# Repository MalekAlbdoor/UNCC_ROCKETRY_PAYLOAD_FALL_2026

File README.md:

# UNCC Rocketry Payload, Fall 2026

Custom avionics board for the UNC Charlotte rocketry club's transonic payload. It logs flight data, tracks position, sends live telemetry and pad status to a ground station, and controls an onboard camera.

## Layout

The schematic is split into hierarchical sheets, all tied together on the root sheet:

| Sheet | Contents |
|---|---|
| POWER | 5V buck, 3.3V regulator, power LED, bring-up jumpers and camera power switch |
| MCU | Microcontroller, clock, reset/boot, battery voltage sense, buzzer and status LED |
| SENSORS | Inertial, pressure and environmental sensors |
| RF | LoRa telemetry radio and GPS |
| FLASH | Onboard flight data storage |
| CONNECTORS | Battery input protection, arming switch, debug header, camera and USB-C |

## Tools

Designed in KiCad 10. Open `UNCC_ROCKETRY_PAYLOAD_FALL_2026.kicad_pro` to get started.

No KiCad? Download [Schematic.pdf](Schematic.pdf) to view the full schematic.

## Dashboard
Take a look at live telemetry at telemetry.malekalbdoor.com

## Status

Schematic in progress. Firmware is being developed on breadboarded breakout boards in parallel. PCB layout has not started.

## License

Copyright (c) 2026 Malek Albdoor.

Everything in this repository (schematics, PCB layout, 3D models, firmware and the telemetry dashboard) is licensed under [Creative Commons Attribution-NonCommercial 4.0](LICENSE) (CC BY-NC 4.0).

- **You can** use, copy, modify and share it for noncommercial purposes, such as personal projects, school teams and research.
- **You must** credit both Malek Albdoor and the [Charlotte Rocketry Club](https://www.charlotterocketry.org/) at UNC Charlotte, link back to this repository, and say if you changed anything.
- **You cannot** use it, or anything made from it, to make money without written permission.

Credit it like this:

> Based on the UNCC Rocketry payload board by Malek Albdoor and the Charlotte Rocketry Club at UNC Charlotte (https://www.charlotterocketry.org/), https://github.com/MalekAlbdoor/UNCC_ROCKETRY_PAYLOAD_FALL_2026, CC BY-NC 4.0.

Libraries and KiCad library parts used by this project keep their own licenses.

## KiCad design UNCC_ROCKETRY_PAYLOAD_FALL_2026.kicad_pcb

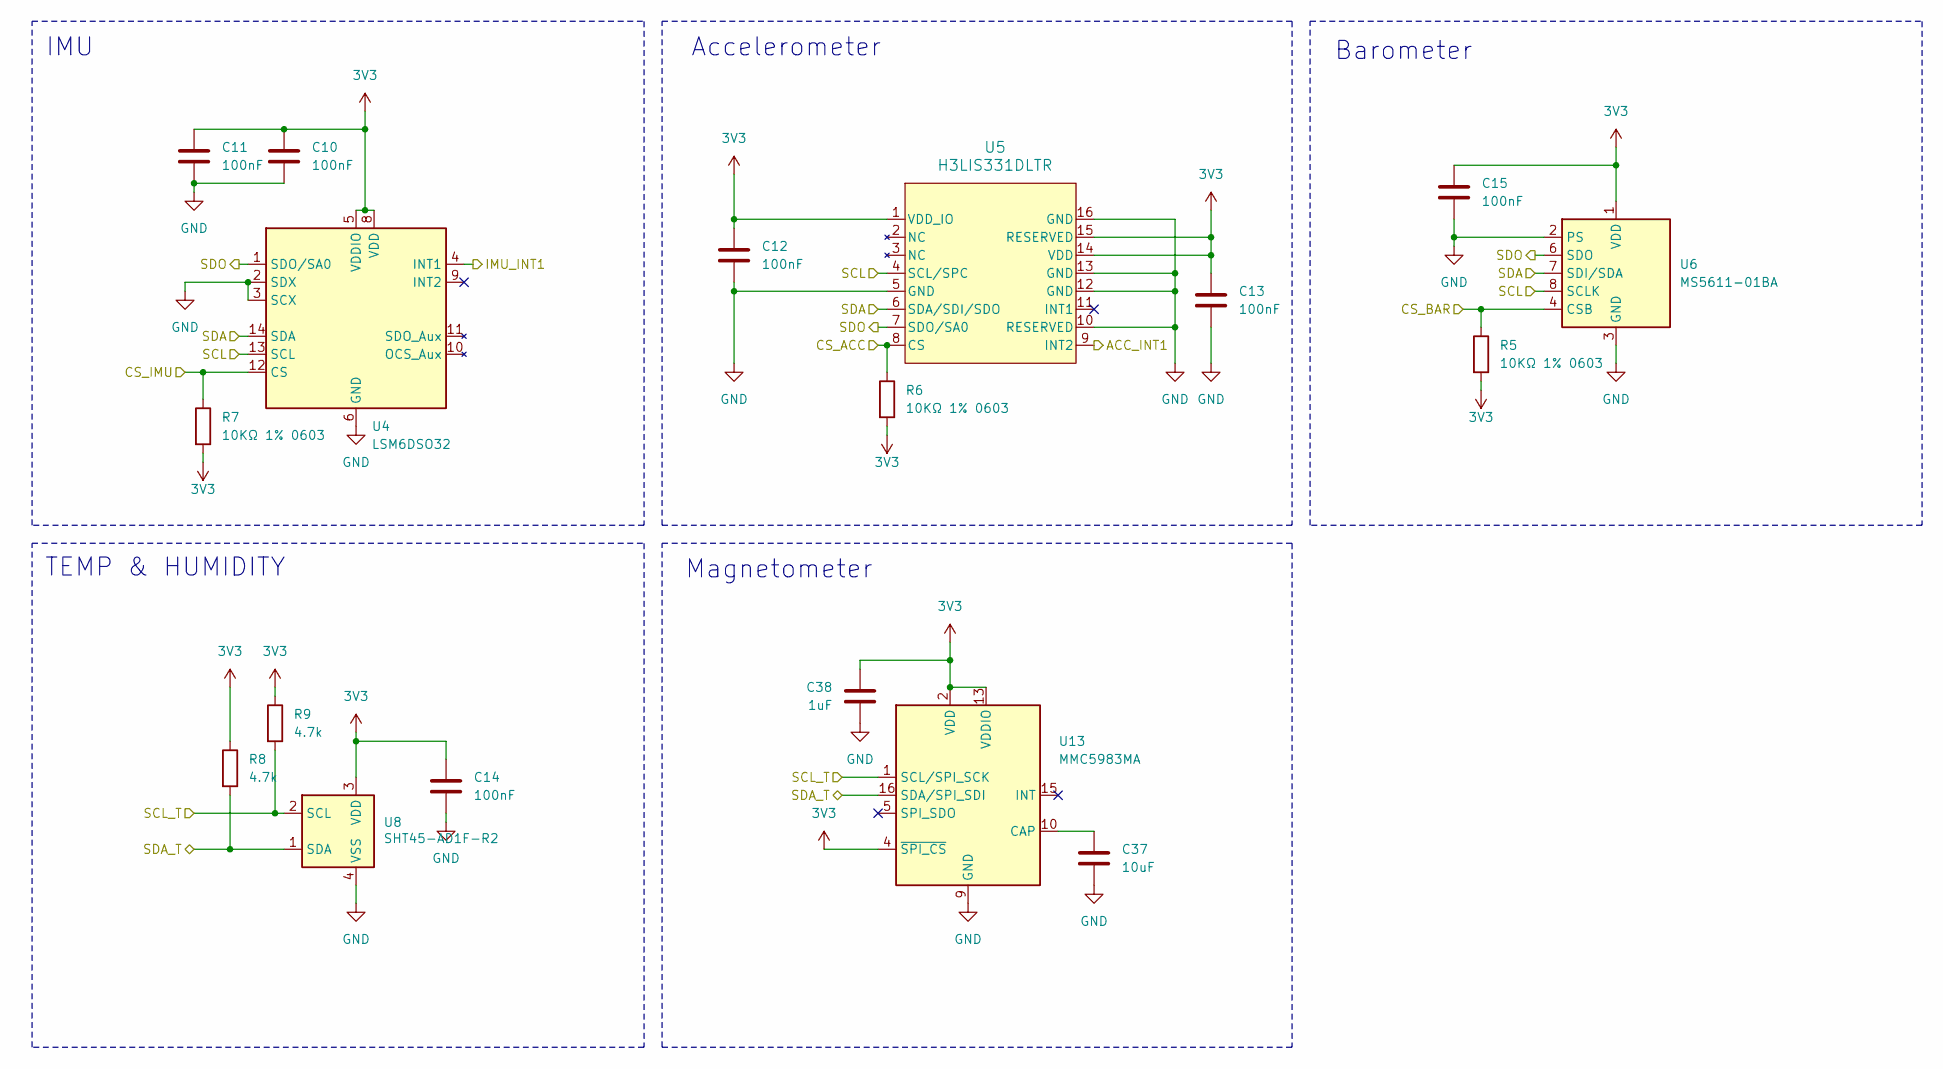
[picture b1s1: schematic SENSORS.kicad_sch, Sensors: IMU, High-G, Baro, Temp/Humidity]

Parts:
C10, C11, C12, C13, C14, C15: 100nF; C_0603_1608Metric_Pad1.08x0.95mm_HandSolder
C37: 10uF; C_0805_2012Metric_Pad1.18x1.45mm_HandSolder
C38: 1uF; C_0603_1608Metric_Pad1.08x0.95mm_HandSolder
R5, R6, R7: 10KΩ 1% 0603; R_0603_1608Metric_Pad0.98x0.95mm_HandSolder
R8, R9: 4.7k; R_0603_1608Metric_Pad0.98x0.95mm_HandSolder
U4: LSM6DSO32; LGA-14_3x2.5mm_P0.5mm_LayoutBorder3x4y
U5: H3LIS331DLTR; LGA-16_3x3mm_P0.5mm_LayoutBorder3x5y
U6: MS5611-01BA; LGA-8_3x5mm_P1.25mm
U8: SHT45-AD1F-R2; Sensirion_DFN-4_1.5x1.5mm_P0.8mm_SHT4x_NoCentralPad
U13: MMC5983MA; LGA-16_3x3mm_P0.5mm

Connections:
3V3: C10.1, C11.1, C12.1, C13.1, C14.1, C15.1, C38.1, R5.2, R6.2, R7.2, R8.1, R9.1, U4.5 (VDDIO), U4.8 (VDD), U5.1 (VDD_IO), U5.14 (VDD), U5.15 (RESERVED), U6.1 (VDD), U8.3 (VDD), U13.2 (VDD), U13.4 (~SPI_CS), U13.13 (VDDIO); also elsewhere on the board
/MCU/ACC_INT1: U5.9 (INT2); also elsewhere on the board
/MCU/CS_ACC: R6.1, U5.8 (CS); also elsewhere on the board
/MCU/CS_BAR: R5.1, U6.4 (CSB), U6.5 (CSB); also elsewhere on the board
/MCU/CS_IMU: R7.1, U4.12 (CS); also elsewhere on the board
/MCU/IMU_INT1: U4.4 (INT1); also elsewhere on the board
/MCU/SCL: U4.13 (SCL), U5.4 (SCL/SPC), U6.8 (SCLK); also elsewhere on the board
/MCU/SDA: U4.14 (SDA), U5.6 (SDA/SDI/SDO), U6.7 (SDI/SDA); also elsewhere on the board
/MCU/SDO: U4.1 (SDO/SA0), U5.7 (SDO/SA0), U6.6 (SDO); also elsewhere on the board
/SCL_T: R9.2, U8.2 (SCL), U13.1 (SCL/SPI_SCK); also elsewhere on the board
/SDA_T: R8.2, U8.1 (SDA), U13.16 (SDA/SPI_SDI); also elsewhere on the board
GND: C10.2, C11.2, C12.2, C13.2, C14.2, C15.2, C37.2, C38.2, U4.2 (SDX), U4.3 (SCX), U4.6 (GND), U4.7 (GND), U5.5 (GND), U5.10 (RESERVED), U5.12 (GND), U5.13 (GND), U5.16 (GND), U6.2 (PS), U6.3 (GND), U8.4 (VSS), U13.9 (GND), U13.11 (GND); also elsewhere on the board
unnamed: C37.1, U13.10 (CAP)

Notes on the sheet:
Magnetometer
TEMP & HUMIDITY
Barometer
Accelerometer
IMU

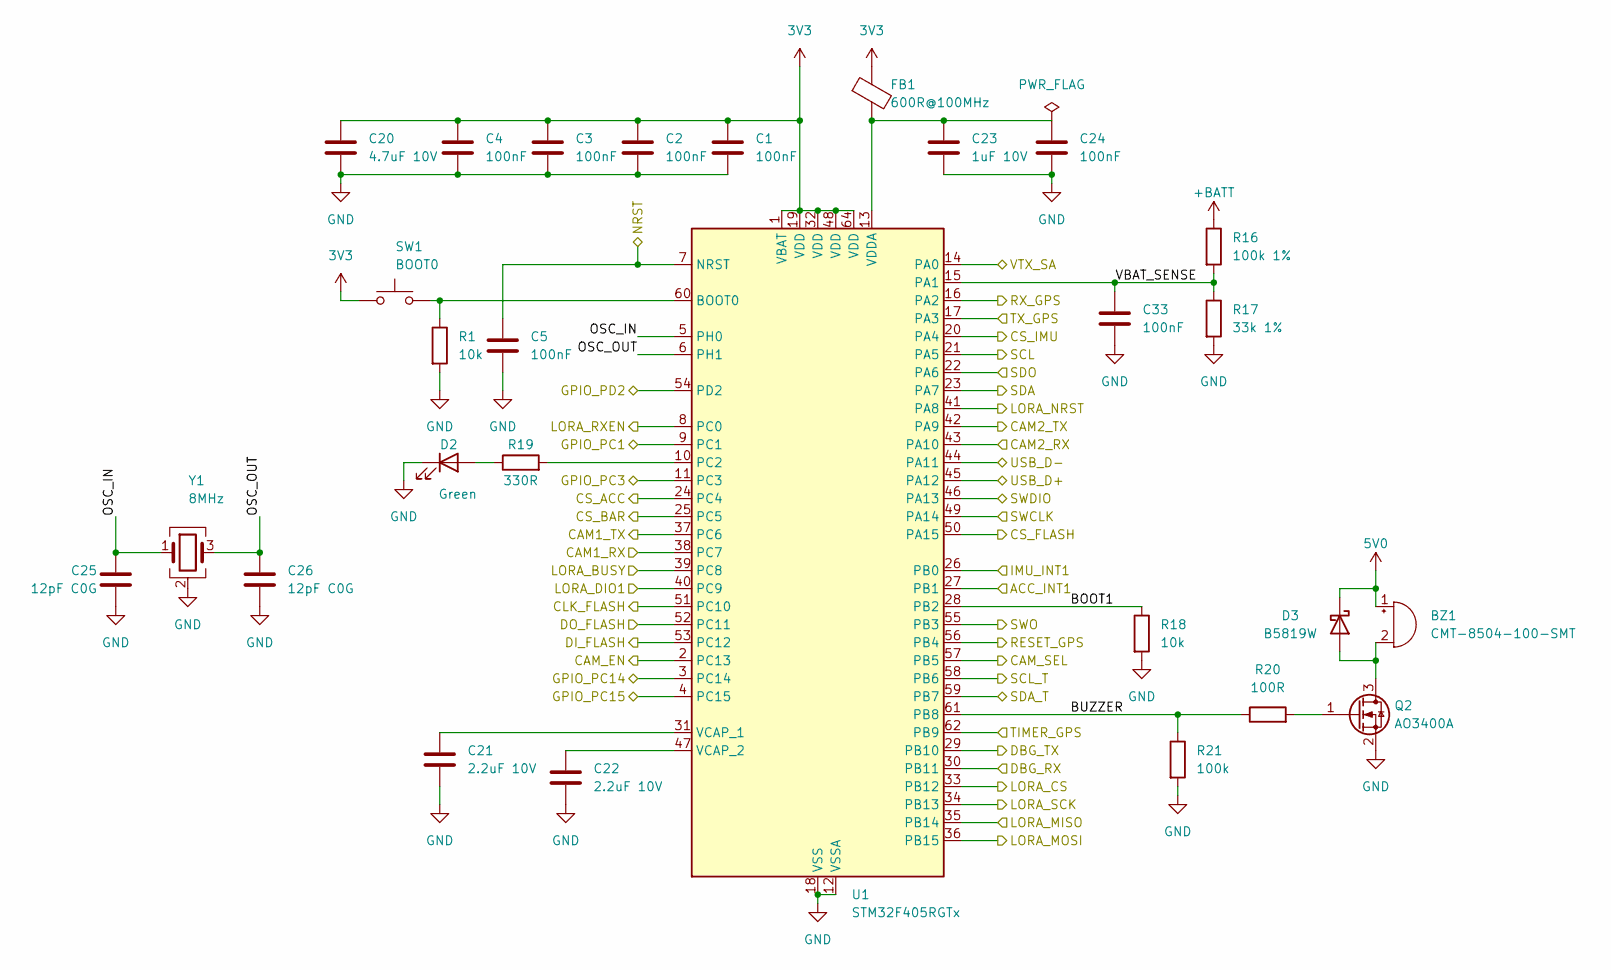
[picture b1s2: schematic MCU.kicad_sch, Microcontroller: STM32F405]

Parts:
BZ1: CMT-8504-100-SMT; MagneticBuzzer_CUI_CMT-8504-100-SMT
C1, C2, C3, C4, C5, C24, C33: 100nF; C_0603_1608Metric_Pad1.08x0.95mm_HandSolder
C20: 4.7uF 10V; C_0603_1608Metric_Pad1.08x0.95mm_HandSolder
C21, C22: 2.2uF 10V; C_0603_1608Metric_Pad1.08x0.95mm_HandSolder
C23: 1uF 10V; C_0603_1608Metric_Pad1.08x0.95mm_HandSolder
C25, C26: 12pF C0G; C_0603_1608Metric_Pad1.08x0.95mm_HandSolder
D2: Green; LED_0603_1608Metric_Pad1.05x0.95mm_HandSolder
D3: B5819W; D_SOD-123
FB1: 600R@100MHz; L_0603_1608Metric_Pad1.05x0.95mm_HandSolder
Q2: AO3400A; SOT-23
R1, R18: 10k; R_0603_1608Metric_Pad0.98x0.95mm_HandSolder
R16: 100k 1%; R_0603_1608Metric_Pad0.98x0.95mm_HandSolder
R17: 33k 1%; R_0603_1608Metric_Pad0.98x0.95mm_HandSolder
R19: 330R; R_0603_1608Metric_Pad0.98x0.95mm_HandSolder
R20: 100R; R_0603_1608Metric_Pad0.98x0.95mm_HandSolder
R21: 100k; R_0603_1608Metric_Pad0.98x0.95mm_HandSolder
SW1: BOOT0; SW_SPST_TL3342
U1: STM32F405RGTx; LQFP-64_10x10mm_P0.5mm
Y1: 8MHz; Crystal_SMD_Abracon_ABM3B-4Pin_5.0x3.2mm; MPN ABM3B-8.000MHZ-10-D-1-G-T

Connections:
3V3: C1.1, C2.1, C3.1, C4.1, C20.1, FB1.1, SW1.1, U1.1 (VBAT), U1.19 (VDD), U1.32 (VDD), U1.48 (VDD), U1.64 (VDD); also elsewhere on the board
5V0: BZ1.1 (+), D3.1 (K); also elsewhere on the board
+BATT: R16.1; also elsewhere on the board
/CONNECTORS/CAM1_RX: U1.38 (PC7); also elsewhere on the board
/CONNECTORS/CAM1_TX: U1.37 (PC6); also elsewhere on the board
/CONNECTORS/CAM2_RX: U1.43 (PA10); also elsewhere on the board
/CONNECTORS/CAM2_TX: U1.42 (PA9); also elsewhere on the board
/CONNECTORS/CAM_SEL: U1.57 (PB5); also elsewhere on the board
/CONNECTORS/DBG_RX: U1.30 (PB11); also elsewhere on the board
/CONNECTORS/DBG_TX: U1.29 (PB10); also elsewhere on the board
/CONNECTORS/GPIO_PC1: U1.9 (PC1); also elsewhere on the board
/CONNECTORS/GPIO_PC3: U1.11 (PC3); also elsewhere on the board
/CONNECTORS/GPIO_PC14: U1.3 (PC14); also elsewhere on the board
/CONNECTORS/GPIO_PC15: U1.4 (PC15); also elsewhere on the board
/CONNECTORS/NRST: C5.1, U1.7 (NRST); also elsewhere on the board
/CONNECTORS/SWCLK: U1.49 (PA14); also elsewhere on the board
/CONNECTORS/SWDIO: U1.46 (PA13); also elsewhere on the board
/CONNECTORS/SWO: U1.55 (PB3); also elsewhere on the board
/CONNECTORS/USB_D+: U1.45 (PA12); also elsewhere on the board
/CONNECTORS/USB_D-: U1.44 (PA11); also elsewhere on the board
/CONNECTORS/VTX_SA: U1.14 (PA0); also elsewhere on the board
/FLASH/CLK_FLASH: U1.51 (PC10); also elsewhere on the board
/FLASH/CS_FLASH: U1.50 (PA15); also elsewhere on the board
/FLASH/DI_FLASH: U1.53 (PC12); also elsewhere on the board
/FLASH/DO_FLASH: U1.52 (PC11); also elsewhere on the board
/MCU/ACC_INT1: U1.27 (PB1); also elsewhere on the board
/MCU/BOOT1: R18.1, U1.28 (PB2)
/MCU/BUZZER: R20.1, R21.1, U1.61 (PB8)
/MCU/CAM_EN: U1.2 (PC13); also elsewhere on the board
/MCU/CS_ACC: U1.24 (PC4); also elsewhere on the board
/MCU/CS_BAR: U1.25 (PC5); also elsewhere on the board
/MCU/CS_IMU: U1.20 (PA4); also elsewhere on the board
/MCU/GPIO_PD2: U1.54 (PD2)
/MCU/IMU_INT1: U1.26 (PB0); also elsewhere on the board
/MCU/LORA_BUSY: U1.39 (PC8); also elsewhere on the board
/MCU/LORA_CS: U1.33 (PB12); also elsewhere on the board
/MCU/LORA_DIO1: U1.40 (PC9); also elsewhere on the board
/MCU/LORA_MISO: U1.35 (PB14); also elsewhere on the board
/MCU/LORA_MOSI: U1.36 (PB15); also elsewhere on the board
/MCU/LORA_NRST: U1.41 (PA8); also elsewhere on the board
/MCU/LORA_RXEN: U1.8 (PC0); also elsewhere on the board
/MCU/LORA_SCK: U1.34 (PB13); also elsewhere on the board
/MCU/OSC_IN: C25.1, U1.5 (PH0), Y1.1
/MCU/OSC_OUT: C26.1, U1.6 (PH1), Y1.3
/MCU/RESET_GPS: U1.56 (PB4); also elsewhere on the board
/MCU/RX_GPS: U1.16 (PA2); also elsewhere on the board
/MCU/SCL: U1.21 (PA5); also elsewhere on the board
/MCU/SDA: U1.23 (PA7); also elsewhere on the board
/MCU/SDO: U1.22 (PA6); also elsewhere on the board
/MCU/TIMER_GPS: U1.62 (PB9); also elsewhere on the board
/MCU/TX_GPS: U1.17 (PA3); also elsewhere on the board
/MCU/VBAT_SENSE: C33.1, R16.2, R17.1, U1.15 (PA1)
/SCL_T: U1.58 (PB6); also elsewhere on the board
/SDA_T: U1.59 (PB7); also elsewhere on the board
GND: C1.2, C2.2, C3.2, C4.2, C5.2, C20.2, C21.2, C22.2, C23.2, C24.2, C25.2, C26.2, C33.2, D2.1 (K), Q2.2 (S), R1.2, R17.2, R18.2, R21.2, U1.12 (VSSA), U1.18 (VSS), U1.63 (VSS), Y1.2 (G), Y1.4 (G); also elsewhere on the board
unnamed: BZ1.2 (-), D3.2 (A), Q2.3 (D)
unnamed: D2.2 (A), R19.1
unnamed: Q2.1 (G), R20.2
unnamed: R1.1, SW1.2, U1.60 (BOOT0)
unnamed: R19.2, U1.10 (PC2)
unnamed: C21.1, U1.31 (VCAP_1)
unnamed: C22.1, U1.47 (VCAP_2)
unnamed: C23.1, C24.1, FB1.2, U1.13 (VDDA)

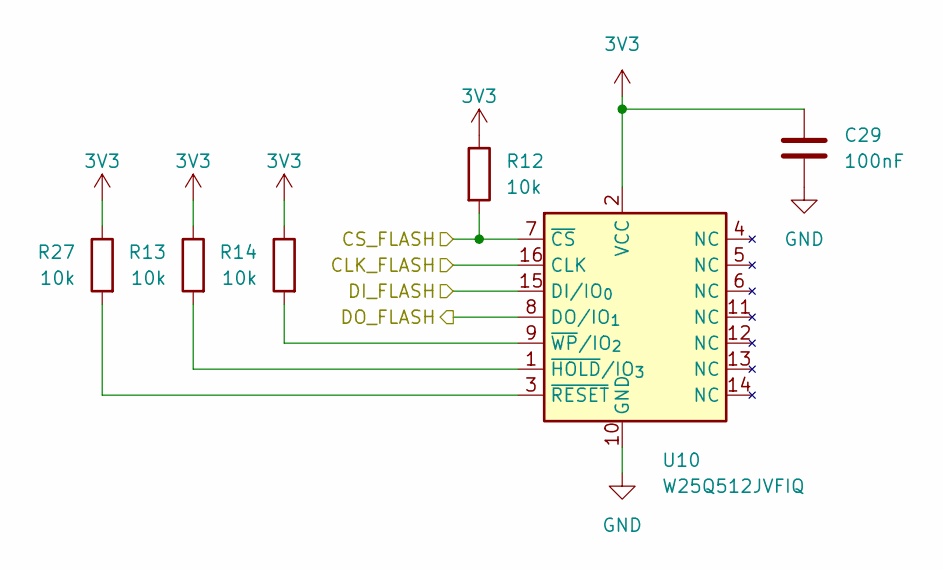
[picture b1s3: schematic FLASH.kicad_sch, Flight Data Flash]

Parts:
C29: 100nF; C_0603_1608Metric_Pad1.08x0.95mm_HandSolder
R12, R13, R14, R27: 10k; R_0603_1608Metric_Pad0.98x0.95mm_HandSolder
U10: W25Q512JVFIQ; SOIC-16W_7.5x10.3mm_P1.27mm

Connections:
3V3: C29.1, R12.1, R13.1, R14.1, R27.1, U10.2 (VCC); also elsewhere on the board
/FLASH/CLK_FLASH: U10.16 (CLK); also elsewhere on the board
/FLASH/CS_FLASH: R12.2, U10.7 (~CS); also elsewhere on the board
/FLASH/DI_FLASH: U10.15 (DI/IO_{0}); also elsewhere on the board
/FLASH/DO_FLASH: U10.8 (DO/IO_{1}); also elsewhere on the board
GND: C29.2, U10.10 (GND); also elsewhere on the board
unnamed: R13.2, U10.1 (~HOLD/IO_{3})
unnamed: R27.2, U10.3 (~RESET)
unnamed: R14.2, U10.9 (~WP/IO_{2})

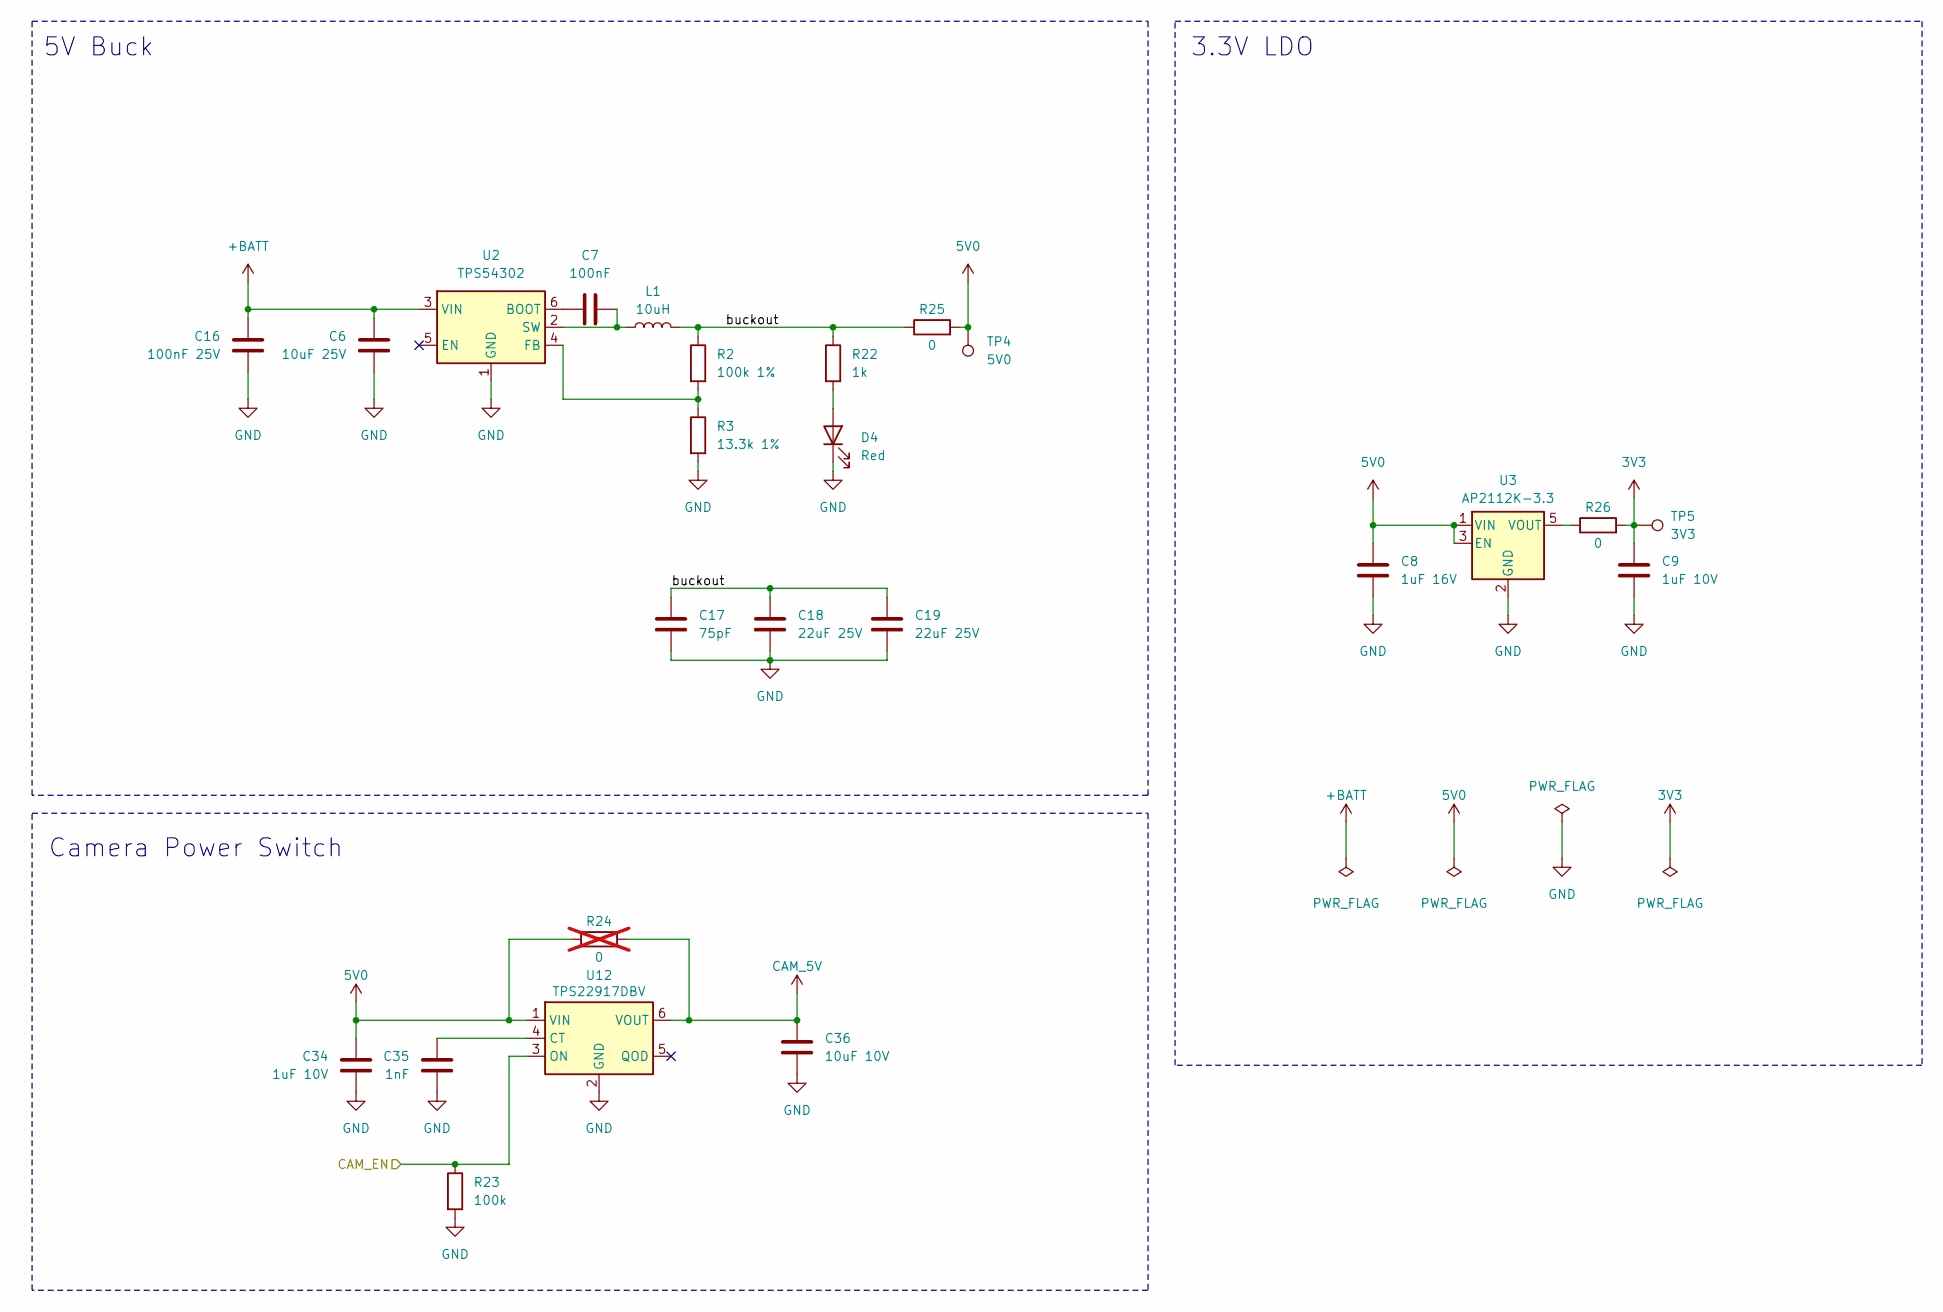
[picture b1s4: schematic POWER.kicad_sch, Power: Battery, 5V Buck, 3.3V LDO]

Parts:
C6: 10uF 25V; C_1206_3216Metric_Pad1.33x1.80mm_HandSolder
C7: 100nF; C_0603_1608Metric_Pad1.08x0.95mm_HandSolder
C8: 1uF 16V; C_0603_1608Metric_Pad1.08x0.95mm_HandSolder
C9, C34: 1uF 10V; C_0603_1608Metric_Pad1.08x0.95mm_HandSolder
C16: 100nF 25V; C_0603_1608Metric_Pad1.08x0.95mm_HandSolder
C17: 75pF; C_0603_1608Metric_Pad1.08x0.95mm_HandSolder
C18, C19: 22uF 25V; C_1206_3216Metric_Pad1.33x1.80mm_HandSolder
C35: 1nF; C_0603_1608Metric_Pad1.08x0.95mm_HandSolder
C36: 10uF 10V; C_0805_2012Metric_Pad1.18x1.45mm_HandSolder
D4: Red; LED_0603_1608Metric_Pad1.05x0.95mm_HandSolder
L1: 10uH; L_Wuerth_XHMI-6060; MPN 74439346100
R2: 100k 1%; R_0603_1608Metric_Pad0.98x0.95mm_HandSolder
R3: 13.3k 1%; R_0603_1608Metric_Pad0.98x0.95mm_HandSolder
R22: 1k; R_0603_1608Metric_Pad0.98x0.95mm_HandSolder
R23: 100k; R_0603_1608Metric_Pad0.98x0.95mm_HandSolder
R24: 0; R_0603_1608Metric_Pad0.98x0.95mm_HandSolder; not fitted
R25, R26: 0; R_0603_1608Metric_Pad0.98x0.95mm_HandSolder
TP4: 5V0; TestPoint_Pad_D1.5mm
TP5: 3V3; TestPoint_Pad_D1.5mm
U2: TPS54302; SOT-23-6
U3: AP2112K-3.3; SOT-23-5
U12: TPS22917DBV; SOT-23-6

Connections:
3V3: C9.1, R26.2, TP5.1 (1_1); also elsewhere on the board
5V0: C8.1, C34.1, R24.1, R25.2, TP4.1 (1_1), U3.1 (VIN), U3.3 (EN), U12.1 (VIN); also elsewhere on the board
+BATT: C6.1, C16.1, U2.3 (VIN); also elsewhere on the board
/MCU/CAM_EN: R23.1, U12.3 (ON); also elsewhere on the board
/POWER/buckout: C17.1, C18.1, C19.1, L1.2, R2.1, R22.1, R25.1
CAM_5V: C36.1, R24.2, U12.6 (VOUT); also elsewhere on the board
GND: C6.2, C8.2, C9.2, C16.2, C17.2, C18.2, C19.2, C34.2, C35.2, C36.2, D4.1 (K), R3.2, R23.2, U2.1 (GND), U3.2 (GND), U12.2 (GND); also elsewhere on the board
unnamed: D4.2 (A), R22.2
unnamed: C7.1, U2.6 (BOOT)
unnamed: R2.2, R3.1, U2.4 (FB)
unnamed: C7.2, L1.1, U2.2 (SW)
unnamed: R26.1, U3.5 (VOUT)
unnamed: C35.1, U12.4 (CT)

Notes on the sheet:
3.3V LDO
5V Buck
Camera Power Switch

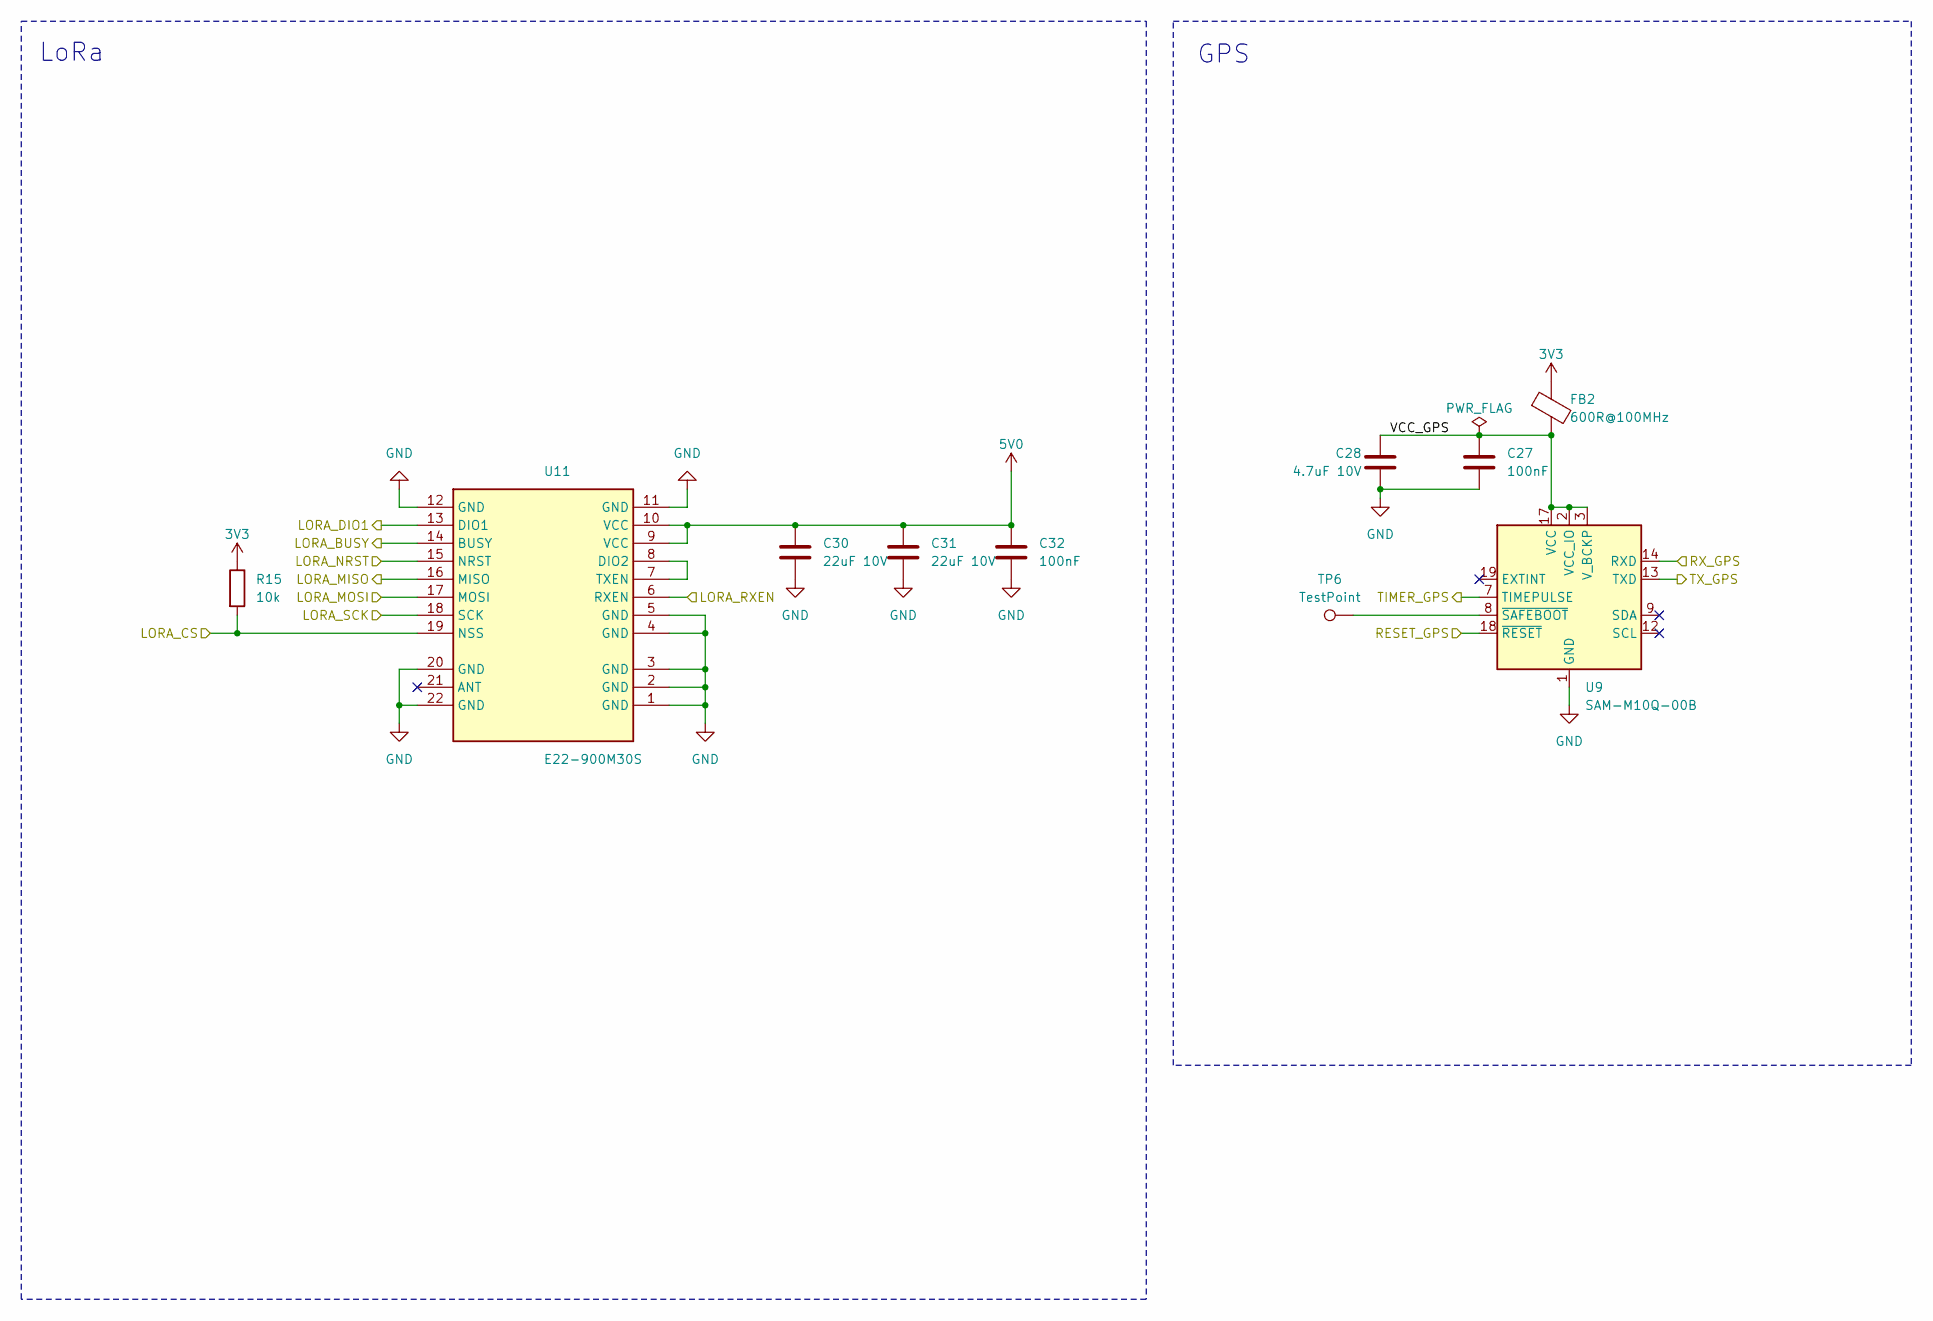
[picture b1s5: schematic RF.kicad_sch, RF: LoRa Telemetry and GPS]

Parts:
C27, C32: 100nF; C_0603_1608Metric_Pad1.08x0.95mm_HandSolder
C28: 4.7uF 10V; C_0603_1608Metric_Pad1.08x0.95mm_HandSolder
C30, C31: 22uF 10V; C_1206_3216Metric_Pad1.33x1.80mm_HandSolder
FB2: 600R@100MHz; L_0603_1608Metric_Pad1.05x0.95mm_HandSolder
R15: 10k; R_0603_1608Metric_Pad0.98x0.95mm_HandSolder
TP6: TestPoint; TestPoint_Pad_D1.5mm
U9: SAM-M10Q-00B; ublox_SAM-M8Q
U11: E22-900M30S; WIRELM-SMD_E22-900M30S

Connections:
3V3: FB2.1, R15.1; also elsewhere on the board
5V0: C30.1, C31.1, C32.1, U11.9 (VCC), U11.10 (VCC); also elsewhere on the board
/MCU/LORA_BUSY: U11.14 (BUSY); also elsewhere on the board
/MCU/LORA_CS: R15.2, U11.19 (NSS); also elsewhere on the board
/MCU/LORA_DIO1: U11.13 (DIO1); also elsewhere on the board
/MCU/LORA_MISO: U11.16 (MISO); also elsewhere on the board
/MCU/LORA_MOSI: U11.17 (MOSI); also elsewhere on the board
/MCU/LORA_NRST: U11.15 (NRST); also elsewhere on the board
/MCU/LORA_RXEN: U11.6 (RXEN); also elsewhere on the board
/MCU/LORA_SCK: U11.18 (SCK); also elsewhere on the board
/MCU/RESET_GPS: U9.18 (~RESET); also elsewhere on the board
/MCU/RX_GPS: U9.14 (RXD); also elsewhere on the board
/MCU/TIMER_GPS: U9.7 (TIMEPULSE); also elsewhere on the board
/MCU/TX_GPS: U9.13 (TXD); also elsewhere on the board
/RF/VCC_GPS: C27.1, C28.1, FB2.2, U9.2 (VCC_IO), U9.3 (V_BCKP), U9.17 (VCC)
GND: C27.2, C28.2, C30.2, C31.2, C32.2, U9.1 (GND), U9.4 (GND), U9.5 (GND), U9.6 (GND), U9.10 (GND), U9.11 (GND), U9.15 (GND), U9.16 (GND), U9.20 (GND), U11.1 (GND), U11.2 (GND), U11.3 (GND), U11.4 (GND), U11.5 (GND), U11.11 (GND), U11.12 (GND), U11.20 (GND), U11.22 (GND); also elsewhere on the board
unnamed: TP6.1 (1_1), U9.8 (~SAFEBOOT)
unnamed: U11.7 (TXEN), U11.8 (DIO2)

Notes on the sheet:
LoRa
GPS

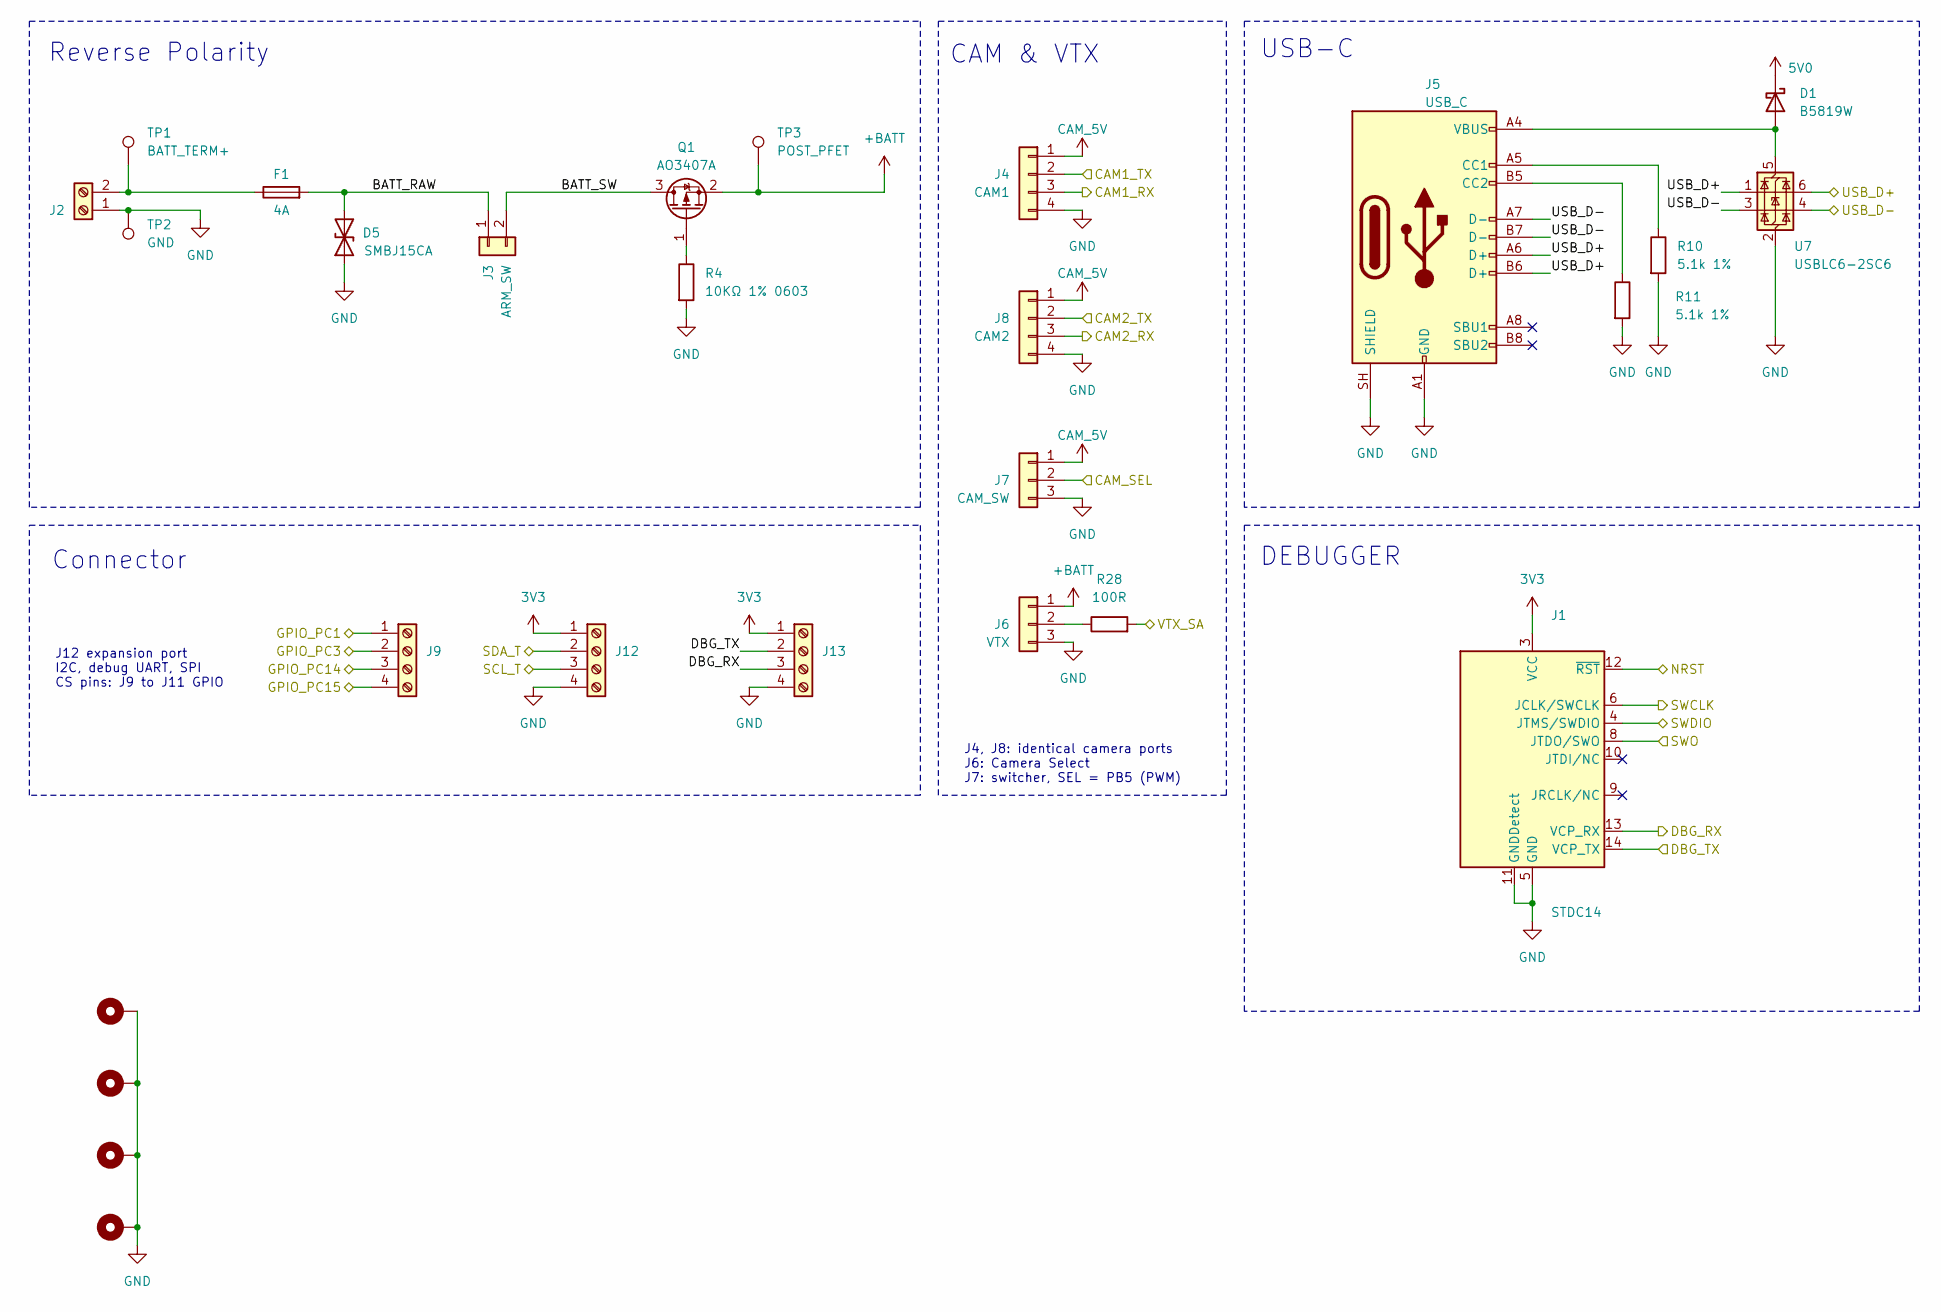
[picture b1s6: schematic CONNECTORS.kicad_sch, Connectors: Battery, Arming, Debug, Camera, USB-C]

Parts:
D1: B5819W; D_SOD-123
D5: SMBJ15CA; D_SMB
F1: 4A; Fuse_Littelfuse-NANO2-451_453; MPN 0451004.MRL
H2, H3, H4, H5: MountingHole_Pad; MountingHole_3.2mm_M3_Pad
J1: STDC14; PinHeader_2x07_P1.27mm_Vertical_SMD
J2: BATT; JST_XH_B2B-XH-A_1x02_P2.50mm_Vertical
J3: ARM_SW; JST_XH_B2B-XH-A_1x02_P2.50mm_Vertical
J4: CAM1; JST_PH_B4B-PH-K_1x04_P2.00mm_Vertical
J5: USB_C; USB_C_Receptacle_HRO_TYPE-C-31-M-12
J6: VTX; JST_XH_B3B-XH-A_1x03_P2.50mm_Vertical
J7: CAM_SW; JST_PH_B3B-PH-K_1x03_P2.00mm_Vertical
J8: CAM2; JST_PH_B4B-PH-K_1x04_P2.00mm_Vertical
J9, J12, J13: Screw_Terminal_01x04; TerminalBlock_Phoenix_PT-1,5-4-3.5-H_1x04_P3.50mm_Horizontal
Q1: AO3407A; SOT-23
R4: 10KΩ 1% 0603; R_0603_1608Metric_Pad0.98x0.95mm_HandSolder
R10, R11: 5.1k 1%; R_0603_1608Metric_Pad0.98x0.95mm_HandSolder
R28: 100R; R_0603_1608Metric_Pad0.98x0.95mm_HandSolder
TP1: BATT_TERM+; TestPoint_Pad_D1.5mm
TP2: GND; TestPoint_Pad_D1.5mm
TP3: POST_PFET; TestPoint_Pad_D1.5mm
U7: USBLC6-2SC6; SOT-23-6

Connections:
3V3: J1.3 (VCC), J12.1, J13.1; also elsewhere on the board
5V0: D1.1 (K); also elsewhere on the board
+BATT: J6.1, Q1.2 (S), TP3.1 (1_1); also elsewhere on the board
/CONNECTORS/BATT_RAW: D5.2 (A2), F1.2, J3.1
/CONNECTORS/BATT_SW: J3.2, Q1.3 (D)
/CONNECTORS/CAM1_RX: J4.3; also elsewhere on the board
/CONNECTORS/CAM1_TX: J4.2; also elsewhere on the board
/CONNECTORS/CAM2_RX: J8.3; also elsewhere on the board
/CONNECTORS/CAM2_TX: J8.2; also elsewhere on the board
/CONNECTORS/CAM_SEL: J7.2; also elsewhere on the board
/CONNECTORS/DBG_RX: J1.13 (VCP_RX), J13.3; also elsewhere on the board
/CONNECTORS/DBG_TX: J1.14 (VCP_TX), J13.2; also elsewhere on the board
/CONNECTORS/GPIO_PC1: J9.1; also elsewhere on the board
/CONNECTORS/GPIO_PC3: J9.2; also elsewhere on the board
/CONNECTORS/GPIO_PC14: J9.3; also elsewhere on the board
/CONNECTORS/GPIO_PC15: J9.4; also elsewhere on the board
/CONNECTORS/NRST: J1.12 (~RST); also elsewhere on the board
/CONNECTORS/SWCLK: J1.6 (JCLK/SWCLK); also elsewhere on the board
/CONNECTORS/SWDIO: J1.4 (JTMS/SWDIO); also elsewhere on the board
/CONNECTORS/SWO: J1.8 (JTDO/SWO); also elsewhere on the board
/CONNECTORS/USB_D+: J5.A6 (D+), J5.B6 (D+), U7.1 (I/O1), U7.6 (I/O1); also elsewhere on the board
/CONNECTORS/USB_D-: J5.A7 (D-), J5.B7 (D-), U7.3 (I/O2), U7.4 (I/O2); also elsewhere on the board
/CONNECTORS/VTX_SA: R28.2; also elsewhere on the board
/SCL_T: J12.3; also elsewhere on the board
/SDA_T: J12.2; also elsewhere on the board
CAM_5V: J4.1, J7.1, J8.1; also elsewhere on the board
GND: D5.1 (A1), H2.1 (1_1), H3.1 (1_1), H4.1 (1_1), H5.1 (1_1), J1.5 (GND), J1.7 (GND), J1.11 (GNDDetect), J2.1, J4.4, J5.A1 (GND), J5.A12 (GND), J5.B1 (GND), J5.B12 (GND), J5.SH (SHIELD), J6.3, J7.3, J8.4, J12.4, J13.4, R4.2, R10.2, R11.2, TP2.1 (1_1), U7.2 (GND); also elsewhere on the board
unnamed: D1.2 (A), J5.A4 (VBUS), J5.A9 (VBUS), J5.B4 (VBUS), J5.B9 (VBUS), U7.5 (VBUS)
unnamed: F1.1, J2.2, TP1.1 (1_1)
unnamed: J5.A5 (CC1), R10.1
unnamed: J5.B5 (CC2), R11.1
unnamed: J6.2, R28.1
unnamed: Q1.1 (G), R4.1

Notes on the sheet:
USB-C
Reverse Polarity
CAM & VTX
DEBUGGER
Connector
J12 expansion port I2C, debug UART, SPI CS pins: J9 to J11 GPIO
J4, J8: identical camera ports J6: Camera Select J7: switcher, SEL = PB5 (PWM)

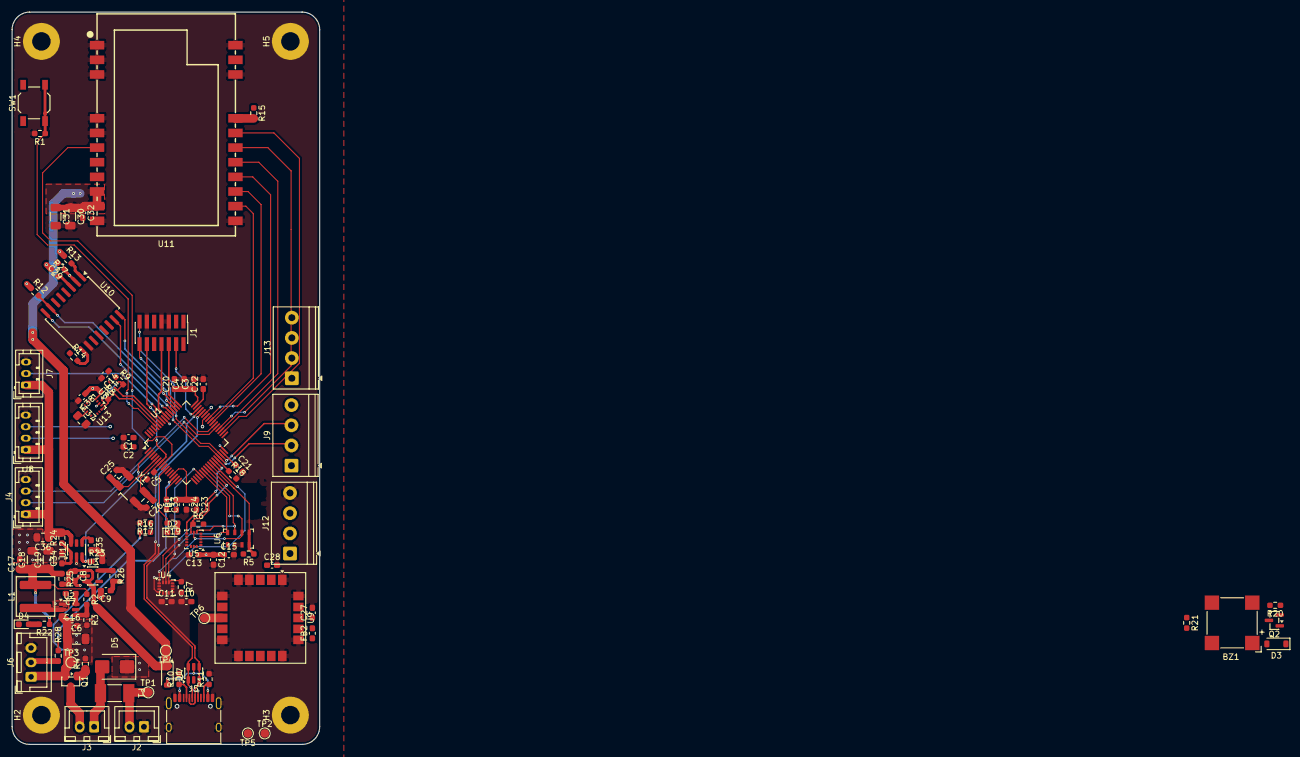
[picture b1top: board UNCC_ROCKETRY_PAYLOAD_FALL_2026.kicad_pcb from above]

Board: 4 copper layers, 53.3 x 127.0 mm, 114 parts (0 on the bottom side), 85 nets.
